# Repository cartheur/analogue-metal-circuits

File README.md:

## analogue-metal-circuits

A collection of (analogue) circuits for a foray into the _metal_ project. A development tracker.

## What is in here

* 01 Getting Started

Where to get started: A tutorial project from KiCad.

* 02 Rodney Beacon

A project first set as a wire-wrap, it divides the frequency of a 555 timer. This board is for an experiment to production.

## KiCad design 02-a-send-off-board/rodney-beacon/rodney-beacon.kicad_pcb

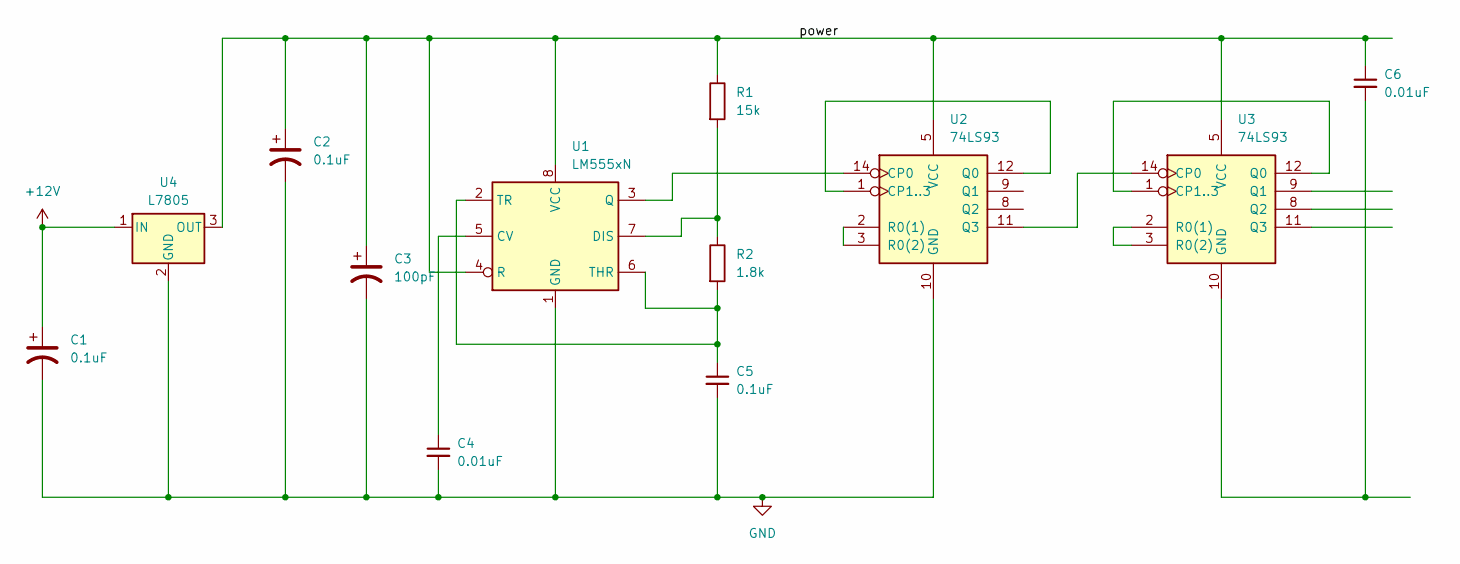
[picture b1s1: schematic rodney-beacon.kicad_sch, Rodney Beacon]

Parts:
C1, C2: 0.1uF; CP_Elec_3x5.3
C3: 100pF; CP_Elec_3x5.3
C4, C6: 0.01uF; C_0201_0603Metric
C5: 0.1uF; C_0201_0603Metric
R1: 15k; R_0201_0603Metric
R2: 1.8k; R_0201_0603Metric
U1: LM555xN; DIP-8_W7.62mm
U2, U3: 74LS93; DIP-14_W7.62mm
U4: L7805; TO-220-3_Horizontal_TabDown

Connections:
+12V: C1.1, U4.1 (IN)
/power: C2.1, C3.1, C6.1, R1.1, U1.4 (R), U1.8 (VCC), U2.5 (VCC), U3.5 (VCC), U4.3 (OUT)
GND: C1.2, C2.2, C3.2, C4.2, C5.2, U1.1 (GND), U2.10 (GND), U4.2 (GND)
unnamed: C4.1, U1.5 (CV)
unnamed: R1.2, R2.1, U1.7 (DIS)
unnamed: U1.3 (Q), U2.14 (CP0)
unnamed: C5.1, R2.2, U1.2 (TR), U1.6 (THR)
unnamed: U2.1 (CP1..3), U2.12 (Q0)
unnamed: U2.11 (Q3), U3.14 (CP0)
unnamed: U2.2 (R0(1)), U2.3 (R0(2))
unnamed: U3.1 (CP1..3), U3.12 (Q0)
unnamed: C6.2, U3.10 (GND)
unnamed: U3.2 (R0(1)), U3.3 (R0(2))

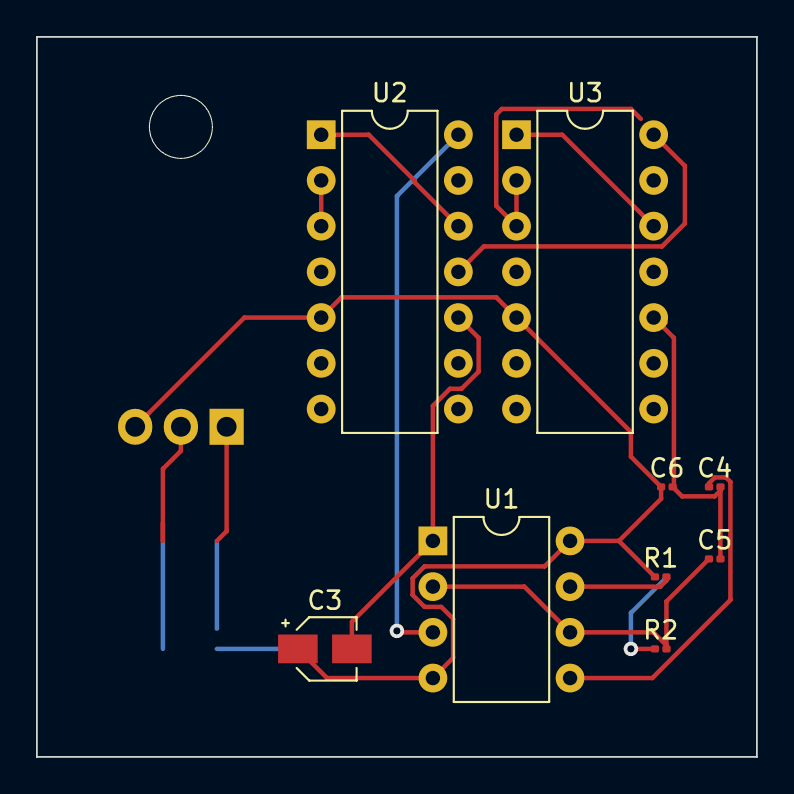
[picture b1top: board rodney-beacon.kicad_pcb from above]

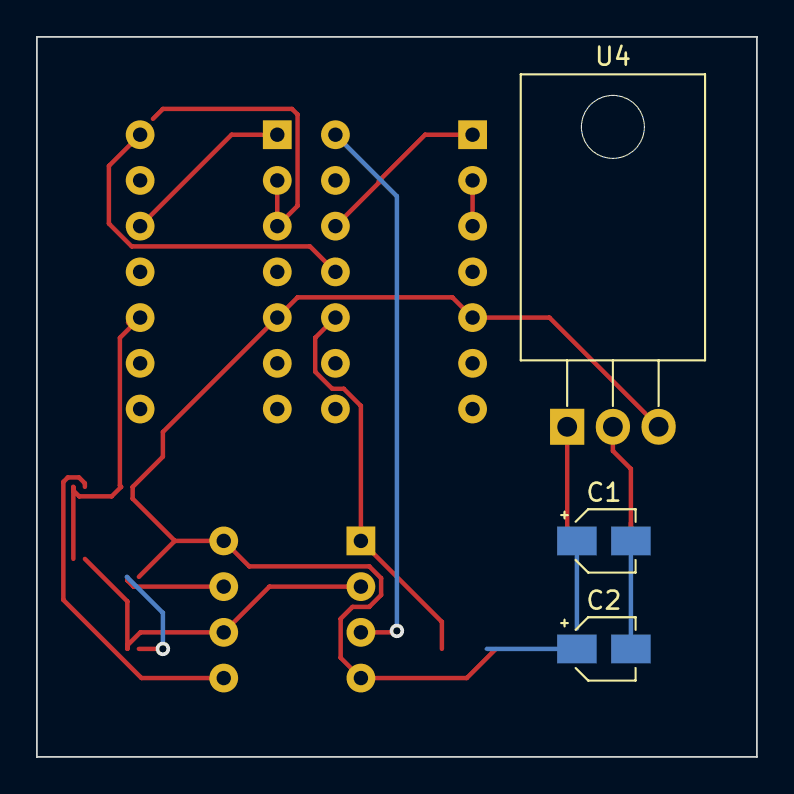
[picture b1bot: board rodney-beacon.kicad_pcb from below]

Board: 2 copper layers, 40.0 x 40.0 mm, 12 parts (3 on the bottom side), 13 nets.

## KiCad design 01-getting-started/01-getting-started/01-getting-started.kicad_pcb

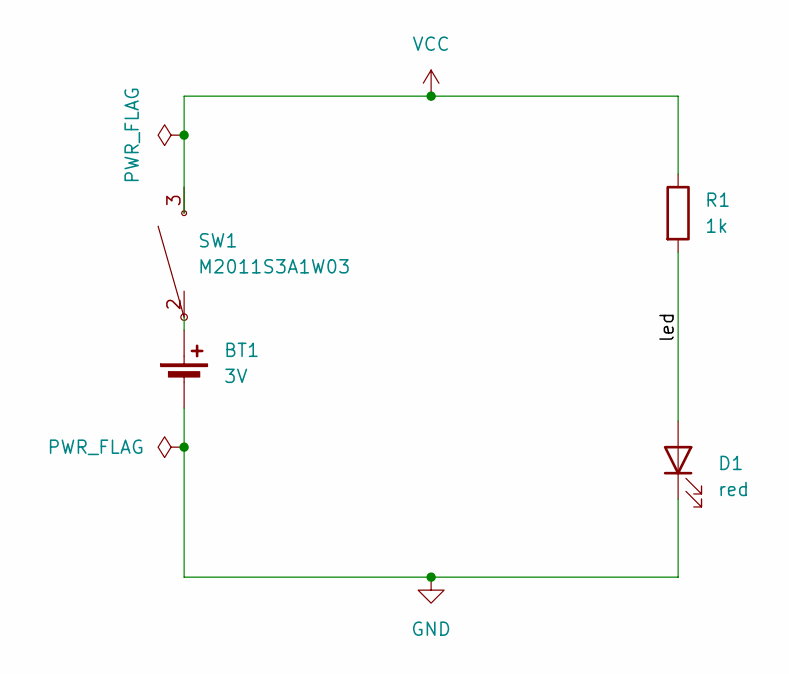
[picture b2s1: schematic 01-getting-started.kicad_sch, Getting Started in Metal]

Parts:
BT1: 3V; BatteryHolder_Keystone_1058_1x2032
D1: red; LED_D5.0mm
R1: 1k; R_Axial_DIN0309_L9.0mm_D3.2mm_P12.70mm_Horizontal
SW1: M2011S3A1W03; Switch_Toggle_SPST_NKK_M2011S3A1x03

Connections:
/led: D1.2 (A), R1.2
GND: BT1.2 (-), D1.1 (K)
unnamed: BT1.1 (+), SW1.2 (A)
VCC: R1.1, SW1.3 (B)

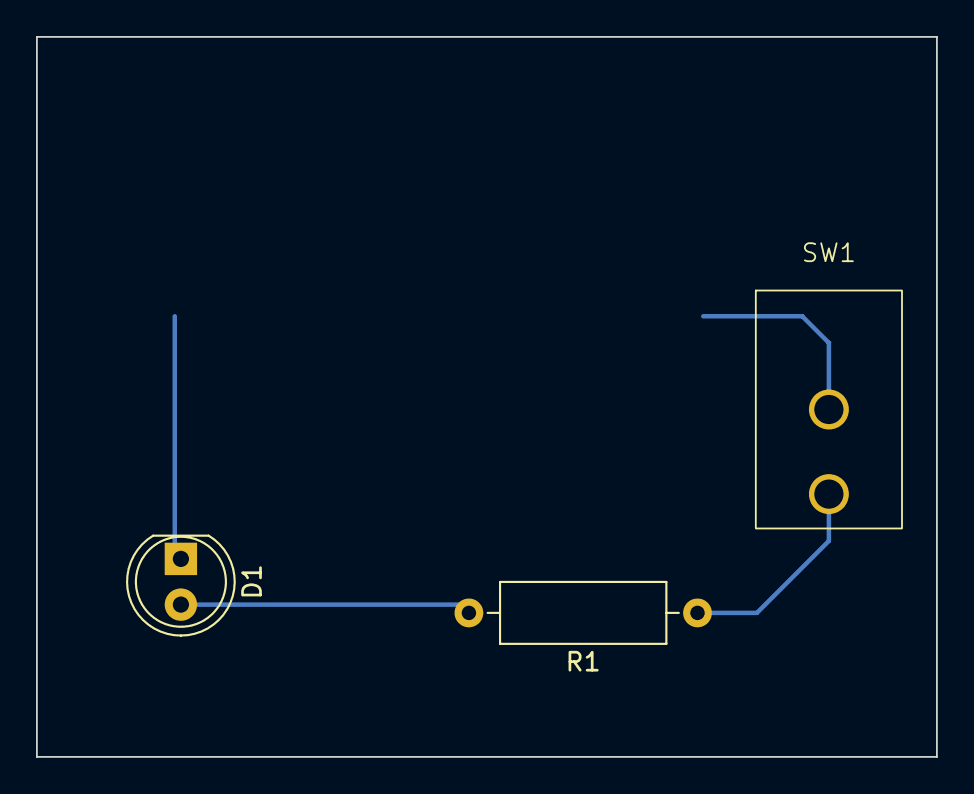
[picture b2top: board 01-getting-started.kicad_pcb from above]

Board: 2 copper layers, 50.0 x 40.0 mm, 4 parts (1 on the bottom side), 4 nets.

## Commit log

2023-11-27 Add new file for ReadMe
2023-11-27 Add getting-started project files
2023-11-27 Add circuit design and BoM
2023-11-27 Add .gitignore for KiCad backup files
2023-11-27 Add finished project
2023-11-27 Remove backup file
2023-11-27 Update BoM
2023-11-27 Add next project
2023-11-27 Add second project to ReadMe
2023-11-28 Add schematic to project
2023-11-28 Update design file
2023-11-28 Add BoM
2023-12-02 Add source schematic
